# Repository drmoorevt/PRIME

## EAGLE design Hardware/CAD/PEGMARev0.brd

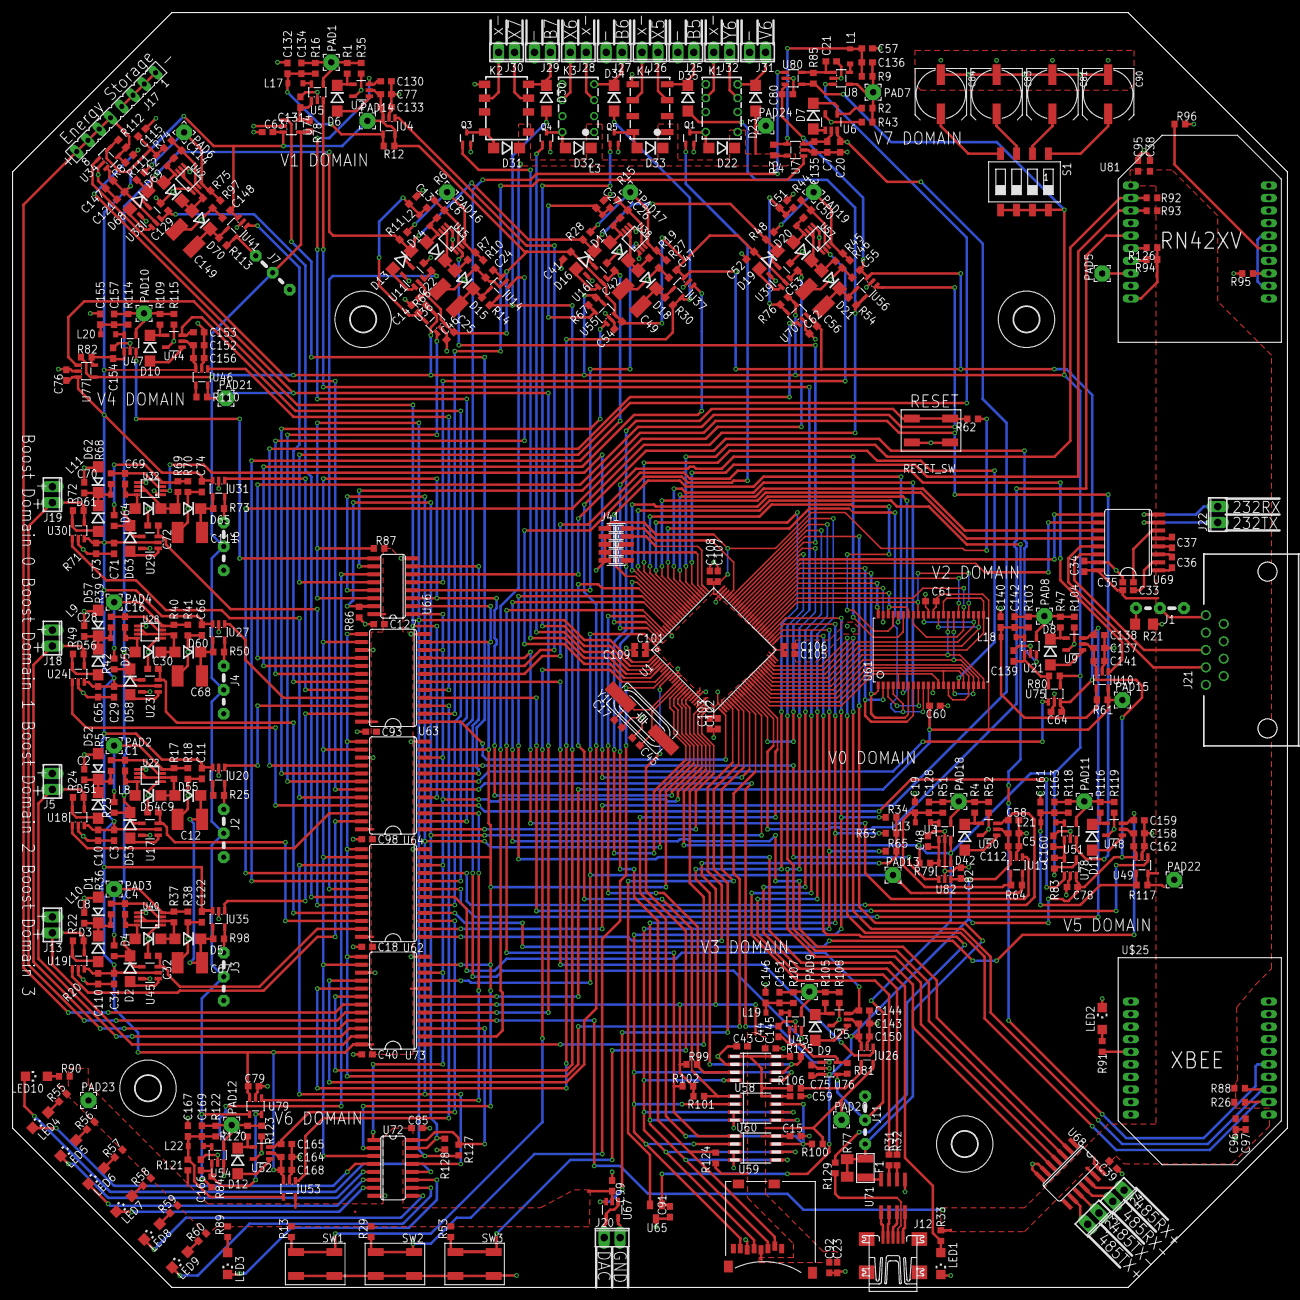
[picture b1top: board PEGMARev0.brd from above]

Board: 2 copper layers, 203.2 x 203.2 mm, 508 parts (0 on the bottom side), 341 nets.

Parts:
C1, C4, C6, C16, C26, C50, C69, C114: 4.7pF; C0603
C2, C8, C13, C27, C28, C51, C70, C115: 22uF; C0603
C3, C5, C7, C10, C11, C14, C15, C18, C24, C29, C31, C33, C34, C35, C36, C37, C38, C39, C40, C41, C44, C46, C47, C52, C54, C55, C59, C60, C61, C62, C63, C64, C65, C66, C71, C73, C74, C75, C76, C77, C78, C79, C80, C82, C85, C91, C92, C93, C96, C98, C99, C101, C102, C103, C105, C106, C107, C108, C109, C110, C112, C121, C122, C127, C133, C135, C137, C141, C143, C147, C148, C150, C152, C156, C158, C162, C164, C168: .1uF; C0603
C9, C19, C20, C22, C23, C30, C32, C42, C53, C57, C58, C72, C95, C97, C129, C130, C132, C138, C140, C144, C146, C153, C155, C159, C161, C165, C167: 10uF; C0603
C12, C25, C49, C56, C67, C68, C111, C149: 100uF Tantalum; C1812
C17, C45: 16pF; C0603
C21, C48, C131, C139, C145, C154, C160, C166: 4.7uF; C0603
C43: .22uF; C0603
C81, C83, C84, C90: 220uF; UD-8X10_NICHICON
C128, C134, C136, C142, C151, C157, C163, C169: 33pF; C0603
D1, D52, D57, D62: TPSMA11HE3; DO214AC
D2, D3, D4, D5, D6, D7, D8, D9, D10, D11, D12, D13, D14, D15, D16, D17, D18, D19, D20, D21, D22, D23, D30, D31, D32, D33, D34, D35, D42, D51, D53, D54, D55, D56, D58, D59, D60, D61, D63, D64, D65, D68, D69, D70: LSM115JE3; DO214BA
F1: MS-USMF010; FUSE(1210)
J1, J2, J3, J4, J6, J11: 04C
J5, J13, J18, J19, J20, J22, J23, J24, J25, J26, J27, J28, J29, J30, J31, J32: 2POL254
J7: Molex 22-28-4030; 04C
J12: MINI-USB-UX60A-MB-5ST; UX60A-MB-5ST
J17: FE08
J21: D-SUB9-H2M09RA; H2M09RA
J41: FTSH-105-02-F-D; 1296-10
K1: G6KU-2P-Y
K2: G6KU-2F-Y
K3: G6K-2P
K4: G6K-2G
L1, L2, L3, L4, L8, L9, L10, L11, L12, L13, L17, L18, L19, L20, L21, L22: 4.7uH; L1008/2520METRIC
LED1, LED2, LED3, LED4, LED5, LED6, LED7, LED8, LED9, LED10: CHIPLED_1206
PAD1, PAD2, PAD3, PAD4, PAD5, PAD6, PAD7, PAD8, PAD9, PAD10, PAD11, PAD12, PAD13, PAD14, PAD15, PAD16, PAD17, PAD18, PAD19, PAD20, PAD21, PAD22, PAD23, PAD24: 2,54/1,0
Q1, Q3, Q4, Q5: 2N2222; SOT323
R1, R2, R4, R47, R105, R109, R116, R120: 144k; R0603
R3, R82, R85, R110: .11; R0603
R5, R6, R15, R36, R39, R44, R68, R74: 150k; R0603
R7, R19, R45, R52: 180k; R0603
R8: 30; R0603
R9, R16, R51, R103, R107, R114, R118, R122: 360k; R0603
R10, R18, R27, R35, R38, R41, R43, R46, R70, R97, R104, R108, R115, R119, R123: 75k; R0603
R11, R28, R48: 22k; R0603
R12, R78: .263; R0603
R13, R29, R53, R55, R56, R57, R58, R59, R60, R89, R90: 1K; R0603
R14, R30, R54, R66, R67, R76: 0.10; R0603
R17, R37, R40, R69, R75: 125k; R0603
R20, R23, R42, R71, R111: 60k; R0603
R21: 120; R1206
R22, R98: .033; R0603
R24, R25: .044; R0603
R26, R88, R92, R93, R94, R95, R96, R126: 100k; R0603
R31, R32, R129: 22; R0603
R33, R91: 1k; R0603
R34, R62, R63, R65, R86, R87, R99, R100, R101, R102, R124, R125, R127, R128: 47k; R0603
R49, R50, R112, R113: .066; R0603
R61, R80: .22; R0603
R64, R79: .183; R0603
R72, R73: .132; R0603
R77: 120; M1206
R81, R106: .31; R0603
R83, R117: .174; R0603
R84, R121: .786; R0603
RESET_SW: B3SN-3012P; SWITCH(B3SN)
S1: CT2194MST; SMS-004
SW1, SW2, SW3: B3SN-3012P; SWITCH(B3SN)
U1: STM32F205VG; PZ100
U2, U6, U9, U11, U16, U17, U23, U25, U29, U33, U39, U44, U45, U48, U50, U52, U67: MCP601R; SOT23-5
U3, U5, U8, U21, U43, U47, U51, U54: TPS62240DDC; SOT23-5
U4, U7, U10, U13, U14, U18, U19, U20, U24, U26, U27, U30, U31, U34, U35, U36, U37, U41, U46, U49, U53, U55, U56, U70, U74, U75, U76, U77, U78, U79, U80, U82: MAX4376; SOT23-5
U12: Molex 500873-0816; MICROSD
U15, U22, U28, U32, U38, U40, U42, U57: LM2623; MSOP8
U58: HIH6130; SO-08M
U59, U60: 25AA512; SO-08M
U61: IS61WV51216-10ZSXI; TSOPII-Z44
U62, U63, U64, U73: 74HC4067; SO24W
U65: MAX6520; SOT23
U66, U72: 74HC259; SO16
U68: ADM3491ARZ; SO14
U69: MAX3232E; SO16L
U71: USB6B1; SO08
U81: RN42XV
U$1, U$2, U$3, U$4: 4,1
U$25: XBEE802.15.4; XBEE
Y1: HC49UP

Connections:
485_DE: U1.66, U68.4
!LED4: LED4.C, U72.4
!LED5: LED5.C, U72.5
!LED6: LED6.C, U72.6
!LED7: LED7.C, U72.7
!LED8: LED8.C, U72.9
!LED9: LED9.C, U72.10
!LED10: LED3.C, U72.11
!LED11: LED10.C, U72.12
!SW1: R13.1, SW1.3, SW1.4, U1.7
!SW2: R29.1, SW2.3, SW2.4, U1.8
!SW3: R53.1, SW3.3, SW3.4, U1.9
/RESET_MCU: J41.10, R62.2, RESET_SW.1, RESET_SW.2, U1.14
A16: U1.58, U61.43
A17: U1.59, U61.44
A18: U1.60, U61.28
ADC123_IN1: U1.24, U73.1
ADC123_IN2: U1.25, U64.1
ADC123_IN3: U1.26, U63.1
B0IN: D3.A, R22.2, U19.5
B0INRAW: J13.2, R22.1, U19.4, U73.23
B0LVEN: D2.C, D13.C, D16.C, D19.C, D53.C, D58.C, D63.C, D68.C, R11.1, R20.1, R23.1, R28.1, R42.1, R48.1, R71.1, R111.1, U11.4, U16.4, U17.4, U23.4, U29.4, U33.4, U39.4, U45.4
B0OUT: J3.1, R98.1, U35.5
B0OUTRAW: C12.1, C67.1, D5.C, D55.C, R98.2, U35.4
B1IN: D51.A, R24.2, U18.5
B1INRAW: J5.2, R24.1, U18.4, U73.22
B1OUT: J2.1, R25.1, U20.5
B1OUTRAW: R25.2, U20.4
B2IN: D56.A, R49.2, U24.5
B2INRAW: J18.2, R49.1, U24.4, U73.21
B2OUT: J4.1, R50.1, U27.5
B2OUTRAW: C68.1, D60.C, R50.2, U27.4
B3IN: D61.A, R72.2, U30.5
B3INRAW: J19.2, R72.1, U30.4, U73.20
B3OUT: J6.1, R73.1, U31.5
B3OUTRAW: C111.1, D65.C, R73.2, U31.4
B4IN: C115.2, L12.1, R74.2, R112.2, U34.5
B4INRAW: J17.5, J17.6, J17.7, J17.8, R8.2, R112.1, U34.4, U73.19
B4OUT: J7.1, R113.1, U41.5
B4OUTRAW: C149.1, D70.C, R113.2, U41.4
B5INRAW: C13.2, L2.1, R6.2, R66.1, U36.5
B5OUT: D30.A, R14.1, U14.5, U73.18
B5OUTRAW: C25.1, D15.C, R14.2, U14.4
B6INRAW: C27.2, L3.1, R15.2, R67.1, U55.5
B6OUT: D34.A, R30.1, U37.5, U73.17
B6OUTRAW: C49.1, D18.C, R30.2, U37.4
B7INRAW: C51.2, L4.1, R44.2, R76.1, U70.5
B7OUT: D35.A, R54.1, U56.5, U73.16
B7OUTRAW: C56.1, D21.C, R54.2, U56.4
BOOST4EN: U1.32, U32.2
BOOST5EN: U1.67, U15.2
BOOST6EN: U38.2, U66.4
BOOST7EN: U57.2, U66.5
BOOSTADJ0: C32.1, U45.3, U62.23
BOOSTADJ1: C9.1, U17.3, U62.22
BOOSTADJ2: C30.1, U23.3, U62.21
BOOSTADJ3: C72.1, U29.3, U62.20
BOOSTADJ4: C129.1, U33.3, U62.19
BOOSTADJ5: C22.1, U11.3, U62.18
BOOSTADJ6: C42.1, U16.3, U62.17
BOOSTADJ7: C53.1, U39.3, U62.16
BOOSTINCUR0: U19.1, U64.23
BOOSTINCUR1: U18.1, U64.22
BOOSTINCUR2: U24.1, U64.21
BOOSTINCUR3: U30.1, U64.20
BOOSTINCUR4: U34.1, U64.19
BOOSTINCUR5: U36.1, U64.18
BOOSTINCUR6: U55.1, U64.17
BOOSTINCUR7: U64.16, U70.1
BOOSTOUTCUR0: U35.1, U63.23
BOOSTOUTCUR1: U20.1, U63.22
BOOSTOUTCUR2: U27.1, U63.21
BOOSTOUTCUR3: U31.1, U63.20
BOOSTOUTCUR4: U41.1, U63.19
BOOSTOUTCUR5: U14.1, U63.18
BOOSTOUTCUR6: U37.1, U63.17
BOOSTOUTCUR7: U56.1, U63.16
BT_CTSRTS: U81.12, U81.16
BT_FRST: PAD5.1, U81.8
BT_RST: U1.36, U81.5
BUCKADJ0: C58.1, U50.3, U62.9
BUCKADJ1: C130.1, U2.3, U62.8
BUCKADJ2: C138.1, U9.3, U62.7
BUCKADJ3: C144.1, U25.3, U62.6
BUCKADJ4: C153.1, U44.3, U62.5
BUCKADJ5: C159.1, U48.3, U62.4
BUCKADJ6: C165.1, U52.3, U62.3
BUCKADJ7: C20.1, U6.3, U62.2
BUCKINCUR0: U64.9, U82.1
BUCKINCUR1: U64.8, U74.1
BUCKINCUR2: U64.7, U75.1
BUCKINCUR3: U64.6, U76.1
BUCKINCUR4: U64.5, U77.1
BUCKINCUR5: U64.4, U78.1
BUCKINCUR6: U64.3, U79.1
BUCKINCUR7: U64.2, U80.1
BUCKOUTCUR0: U13.1, U63.9
BUCKOUTCUR1: U4.1, U63.8
BUCKOUTCUR2: U10.1, U63.7
BUCKOUTCUR3: U26.1, U63.6
BUCKOUTCUR4: U46.1, U63.5
BUCKOUTCUR5: U49.1, U63.4
BUCKOUTCUR6: U53.1, U63.3
BUCKOUTCUR7: U7.1, U63.2
BUSVOUT: J2.2, J3.2, J4.2, J6.2, J7.2, J11.2, R66.2, R67.2, R76.2, R78.2, R79.2, R80.2, R81.2, R82.2, R83.2, R84.2, R85.2, S1.5, S1.6, S1.7, S1.8, U1.23, U3.3, U36.4, U55.4, U70.4, U74.4, U75.4, U76.4, U77.4, U78.4, U79.4, U80.4, U82.4
D0: U1.61, U61.1, U61.7
D1: U1.62, U61.2, U61.8
D2: U1.81, U61.3, U61.9
D3: U1.82, U61.4, U61.10
D4: U1.38, U61.5, U61.13
D5: U1.39, U61.14, U61.18
D6: U1.40, U61.15, U61.19
D7: U1.41, U61.16, U61.20
D8: U1.42, U61.21, U61.29
D9: U1.43, U61.22, U61.30
D10: U1.44, U61.23, U61.31
D11: U1.45, U61.24, U61.32
D12: U1.46, U61.25, U61.35
D13: U1.55, U61.26, U61.36
D14: U1.56, U61.27, U61.37
D15: U1.57, U61.38, U61.42
DACOUT1: U1.29, U62.1
DACOUT2: U1.30, U67.3
DOMEN: U1.15, U62.15, U66.13, U72.13
DOMLEN: R87.1, R127.1, U1.1, U66.14, U72.14
DOMRST: R86.1, R128.2, U1.34, U66.15, U72.15
DOMSEL0: U1.18, U62.10, U63.10, U64.10, U66.1, U72.1, U73.10
DOMSEL1: U1.16, U62.11, U63.11, U64.11, U66.2, U72.2, U73.11
DOMSEL2: U1.17, U62.14, U63.14, U64.14, U66.3, U72.3, U73.14
DOMSEL3: U1.33, U62.13, U63.13, U64.13, U73.13
EE0CS: R101.2, U1.91, U60.1
EE1CS: R102.2, U1.95, U59.1
EEHLD: R100.2, U1.37, U59.7, U60.7
EXTVREF: U1.31, U65.2
FSMC_BLN0: U1.97, U61.40
FSMC_BLN1: U1.98, U61.39
FSMC_NE1: U1.88, U61.6
FSMC_NOE: U1.85, U61.41
FSMC_NWE: U1.86, U61.17
HIHALM: R125.2, U1.84, U58.6
HIHCS: R99.2, U1.96, U58.3
JTCK: J41.4, U1.76
JTDI: J41.8, U1.77
JTDO: J41.6, U1.89
JTMS: J41.2, U1.72
K1EN: Q1.2, U1.5
K2EN: Q3.2, U1.4
K3EN: Q4.2, U1.3
K4EN: Q5.2, U1.2
MCUSCK: R65.1, U1.52, U12.5, U58.4, U59.6, U60.6
MCUSDI: R34.1, U1.54, U12.7, U58.5, U59.2, U60.2
MCUSDO: R63.1, U1.53, U12.3, U59.5, U60.5
MCUUSBD+: R32.1, U1.71
MCUUSBD-: R31.1, U1.70
unnamed: C131.1, R78.1, U5.1, U74.5
unnamed: C8.2, D1.C, D3.C, L10.1, R36.2
unnamed: J22.1, U69.7
unnamed: PAD3.1, R20.2, R37.1, R38.2, U40.4
unnamed: C4.1, R36.1, U40.3
unnamed: C2.2, D51.C, D52.C, L8.1, R5.2
unnamed: J22.2, U69.8
unnamed: C4.2, D4.A, L10.2, U40.8
unnamed: D42.C, R4.1, U50.4
unnamed: PAD16.1, R7.1, R10.2, R11.2, U15.4
unnamed: PAD2.1, R17.1, R18.2, R23.2, U22.4
unnamed: C1.1, R5.1, U22.3
unnamed: R126.2, U81.6
unnamed: C1.2, D54.A, L8.2, U22.8
unnamed: C6.1, R6.1, U15.3
unnamed: C6.2, D14.A, L2.2, U15.8
unnamed: L13.1, U3.5
unnamed: D7.C, R2.1, U6.4
unnamed: D4.C, D5.A, R37.2, U40.2, U40.6, U40.7
unnamed: D14.C, D15.A, R7.2, U15.6, U15.7
unnamed: D13.A, U11.1
unnamed: R94.2, U81.7
unnamed: R95.1, U81.13
unnamed: PAD17.1, R19.1, R27.2, R28.2, U38.4
unnamed: J1.2, J21.5
unnamed: C48.1, R79.1, U3.1, U82.5
unnamed: D54.C, D55.A, R17.2, U22.2, U22.6, U22.7
unnamed: D53.A, U17.1
unnamed: C33.1, U69.2
unnamed: C17.2, U1.12, Y1.2
unnamed: C45.1, U1.13, Y1.1
unnamed: D2.A, U45.1
unnamed: C136.2, PAD7.1, R2.2, R9.1, R43.2, U8.4
unnamed: L1.1, U8.5
unnamed: D31.A, K2.8, Q3.1
unnamed: C139.1, R80.1, U21.1, U75.5
unnamed: C26.1, R15.1, U38.3
unnamed: C26.2, D17.A, L3.2, U38.8
unnamed: D6.C, R1.1, U2.4
unnamed: D17.C, D18.A, R19.2, U38.6, U38.7
unnamed: D16.A, U16.1
unnamed: D7.A, U6.1
unnamed: C28.2, D56.C, D57.C, L9.1, R39.2
unnamed: PAD19.1, R45.1, R46.2, R48.2, U57.4
unnamed: C50.1, R44.1, U57.3
unnamed: PAD4.1, R40.1, R41.2, R42.2, U28.4
unnamed: C35.1, U69.6
unnamed: C36.1, U69.1
unnamed: C36.2, U69.3
unnamed: C37.1, U69.4
unnamed: C16.1, R39.1, U28.3
unnamed: C16.2, D59.A, L9.2, U28.8
unnamed: C37.2, U69.5
unnamed: J21.3, U69.14
unnamed: J21.2, U69.13
unnamed: D59.C, D60.A, R40.2, U28.2, U28.6, U28.7
unnamed: J1.3, R21.2
unnamed: D22.A, K1.8, Q1.1
unnamed: C134.2, PAD1.1, R1.2, R16.1, R35.2, U5.4
unnamed: C50.2, D20.A, L4.2, U57.8
unnamed: D20.C, D21.A, R45.2, U57.6, U57.7
unnamed: D19.A, U39.1
unnamed: LED3.A, R89.1
unnamed: C145.1, R81.1, U43.1, U76.5
unnamed: D58.A, U23.1
unnamed: C154.1, R82.1, U47.1, U77.5
unnamed: C160.1, R83.1, U51.1, U78.5
unnamed: C128.2, PAD18.1, R4.2, R51.1, R52.2, U3.4
unnamed: C166.1, R84.1, U54.1, U79.5
unnamed: C21.1, R85.1, U8.1, U80.5
unnamed: C83.+, S1.3
unnamed: C90.+, S1.1
unnamed: C81.+, S1.2
unnamed: LED4.A, R55.1
unnamed: LED5.A, R56.1
unnamed: LED6.A, R57.1
unnamed: LED10.A, R90.1
unnamed: C84.+, S1.4
unnamed: J12.4, R129.2
unnamed: C70.2, D61.C, D62.C, L11.1, R68.2
unnamed: LED7.A, R58.1
unnamed: LED8.A, R59.1
unnamed: LED9.A, R60.1
unnamed: R69.1, R70.2, R71.2, U32.4
unnamed: C69.1, R68.1, U32.3
unnamed: C69.2, D64.A, L11.2, U32.8
unnamed: D64.C, D65.A, R69.2, U32.6, U32.7
unnamed: D63.A, U29.1
unnamed: L17.1, U5.5
unnamed: D6.A, U2.1
unnamed: PAD6.1, R75.1, R97.2, R111.2, U42.4
unnamed: J20.1, U67.1, U67.4
unnamed: C114.1, R74.1, U42.3
unnamed: C114.2, D69.A, L12.2, U42.8
unnamed: D69.C, D70.A, R75.2, U42.2, U42.6, U42.7
unnamed: J32.1, K1.3
unnamed: D68.A, U33.1
unnamed: J32.2, K1.6
unnamed: D32.A, K3.8, Q4.1
unnamed: J28.1, K3.3
unnamed: D23.C, J31.1, K1.4
unnamed: J28.2, K3.6
unnamed: D33.A, K4.8, Q5.1
unnamed: J30.1, K2.3
unnamed: D30.C, J29.1, K2.4
unnamed: J30.2, K2.6
unnamed: R91.1, U$25.15
unnamed: LED2.A, R91.2
unnamed: D34.C, J27.1, K3.4
unnamed: R96.1, U81.15
unnamed: D35.C, J25.1, K4.4
unnamed: J26.1, K4.3
unnamed: J26.2, K4.6
unnamed: D8.C, R47.1, U9.4
unnamed: J24.1, U68.12
unnamed: J24.2, U68.11
unnamed: J23.1, U68.10
unnamed: J23.2, U68.9
unnamed: J12.1, U71.1
unnamed: J12.2, U71.2
unnamed: J12.3, U71.3
unnamed: J12.5, U71.4
unnamed: C142.2, PAD8.1, R47.2, R103.1, R104.2, U21.4
unnamed: L18.1, U21.5
unnamed: D8.A, U9.1
unnamed: D42.A, U50.1
unnamed: D9.C, R105.1, U25.4
unnamed: C151.2, PAD9.1, R105.2, R107.1, R108.2, U43.4
unnamed: L19.1, U43.5
unnamed: D9.A, U25.1
unnamed: D10.C, R109.1, U44.4
unnamed: C157.2, PAD10.1, R109.2, R114.1, R115.2, U47.4
unnamed: L20.1, U47.5
unnamed: D10.A, U44.1
unnamed: D11.C, R116.1, U48.4
unnamed: C163.2, PAD11.1, R116.2, R118.1, R119.2, U51.4
unnamed: L21.1, U51.5
unnamed: D11.A, U48.1
unnamed: D12.C, R120.1, U52.4
unnamed: C169.2, PAD12.1, R120.2, R122.1, R123.2, U54.4
unnamed: L22.1, U54.5
unnamed: D12.A, U52.1
PE: C2.1, C3.1, C5.1, C7.1, C8.1, C9.2, C10.1, C11.1, C12.2, C13.1, C14.1, C15.1, C17.1, C18.1, C19.2, C20.2, C21.2, C22.2, C23.1, C24.1, C25.2, C27.1, C28.1, C29.1, C30.2, C31.1, C32.2, C34.2, C35.2, C38.1, C39.2, C40.1, C41.1, C42.2, C43.1, C44.1, C45.2, C46.1, C47.1, C48.2, C49.2, C51.1, C52.1, C53.2, C54.1, C55.1, C56.2, C57.2, C58.2, C59.1, C60.1, C61.1, C62.1, C63.1, C64.1, C65.1, C66.1, C67.2, C68.2, C70.1, C71.1, C72.2, C73.1, C74.1, C75.1, C76.1, C77.1, C78.1, C79.1, C80.1, C81.-, C82.1, C83.-, C84.-, C85.1, C90.-, C91.1, C92.2, C93.1, C95.1, C96.1, C97.1, C98.1, C99.1, C101.1, C102.1, C103.1, C105.1, C106.1, C107.1, C108.1, C109.1, C110.1, C111.2, C112.1, C115.1, C121.1, C122.1, C127.1, C129.2, C130.2, C131.2, C132.2, C133.1, C135.1, C137.1, C138.2, C139.2, C140.2, C141.1, C143.1, C144.2, C145.2, C146.2, C147.1, C148.1, C149.2, C150.1, C152.1, C153.2, C154.2, C155.2, C156.1, C158.1, C159.2, C160.2, C161.2, C162.1, C164.1, C165.2, C166.2, C167.2, C168.1, D1.A, D52.A, D57.A, D62.A, J5.1, J13.1, J17.1, J17.2, J17.3, J17.4, J18.1, J19.1, J20.2, J25.2, J27.2, J29.2, J31.2, J41.3, J41.5, J41.7, J41.9, K1.5, K2.5, K3.5, K4.5, LED1.C, LED2.C, Q1.3, Q3.3, Q4.3, Q5.3, R10.1, R18.1, R21.1, R27.1, R35.1, R38.1, R41.1, R43.1, R46.1, R52.1, R70.1, R86.2, R94.1, R95.2, R96.2, R97.1, R104.1, R108.1, R115.1, R119.1, R123.1, R126.1, R128.1, RESET_SW.3, RESET_SW.4, SW1.1, SW1.2, SW2.1, SW2.2, SW3.1, SW3.2, U1.10, U1.20, U1.27, U1.74, U1.94, U2.5, U3.2, U4.2, U5.2, U6.5, U7.2, U8.2, U9.5, U10.2, U11.5, U12.6, U13.2, U14.2, U15.1, U15.5, U16.5, U17.5, U18.2, U19.2, U20.2, U21.2, U22.1, U22.5, U23.5, U24.2, U25.5, U26.2, U27.2, U28.1, U28.5, U29.5, U30.2, U31.2, U32.1, U32.5, U33.5, U34.2, U35.2, U36.2, U37.2, U38.1, U38.5, U39.5, U40.1, U40.5, U41.2, U42.1, U42.5, U43.2, U44.5, U45.5, U46.2, U47.2, U48.5, U49.2, U50.5, U51.2, U52.5, U53.2, U54.2, U55.2, U56.2, U57.1, U57.5, U58.2, U59.3, U59.4, U60.3, U60.4, U61.12, U61.34, U62.12, U63.12, U63.15, U64.12, U64.15, U65.3, U66.8, U67.5, U68.6, U68.7, U69.15, U70.2, U71.5, U72.8, U73.12, U73.15, U74.2, U75.2, U76.2, U77.2, U78.2, U79.2, U80.2, U81.10, U82.2, U$25.10
RAWV0: C19.1, C128.1, L13.2, R51.2, R64.2, U13.4
RAWV1: C132.1, C134.1, L17.2, R12.2, R16.2, U4.4
RAWV2: C140.1, C142.1, L18.2, R61.2, R103.2, U10.4
RAWV3: R106.2, U26.4
RAWV4: R110.2, U46.4
RAWV5: C161.1, C163.1, L21.2, R117.2, R118.2, U49.4
RAWV6: C167.1, C169.1, L22.2, R121.2, R122.2, U53.4
RAWV7: C57.1, C136.1, L1.2, R3.2, R9.2, U7.4
SDCS: R124.2, U1.90, U12.2
UART1RX: U1.93, U68.2
UART1TX: U1.92, U68.5
UART3RX: R26.1, U1.48, U$25.2
UART3TX: R88.1, U1.47, U$25.3
UART4RX: R92.1, U1.79, U81.2
UART4TX: R93.1, U1.78, U81.3
UART5RX: U1.83, U69.12
UART5TX: U1.80, U69.11
UART6RX: U1.64, U69.9
UART6TX: U1.63, U69.10
USB5V_F: F1.P$1, J11.3, R77.1, R77.2, U1.68
USBD+: R32.2, U71.6
USBD-: R31.2, U71.7
USBLED: LED1.A, R33.2, U1.69
USB_ID: R129.1, U1.51
V0: C101.2, C102.2, C103.2, C105.2, C106.2, C107.2, C108.2, C109.2, J41.1, PAD13.1, R62.1, R64.1, U1.6, U1.11, U1.19, U1.22, U1.28, U1.49, U1.50, U1.73, U1.75, U1.100, U13.5, U73.9
V1: C3.2, C5.2, C7.2, C10.2, C11.2, C14.2, C18.2, C24.2, C29.2, C31.2, C40.2, C41.2, C46.2, C47.2, C52.2, C54.2, C55.2, C62.2, C63.2, C64.2, C65.2, C66.2, C71.2, C73.2, C74.2, C75.2, C76.2, C77.2, C78.2, C79.2, C80.2, C82.2, C91.2, C93.2, C98.2, C110.2, C112.2, C121.2, C122.2, C127.2, C133.2, C135.2, C137.2, C141.2, C143.2, C147.2, C148.2, C150.2, C152.2, C156.2, C158.2, C162.2, C164.2, C168.2, PAD14.1, R12.1, R87.2, U2.2, U4.3, U4.5, U6.2, U7.3, U9.2, U10.3, U11.2, U13.3, U14.3, U16.2, U17.2, U18.3, U19.3, U20.3, U23.2, U24.3, U25.2, U26.3, U27.3, U29.2, U30.3, U31.3, U33.2, U34.3, U35.3, U36.3, U37.3, U39.2, U41.3, U44.2, U45.2, U46.3, U48.2, U49.3, U50.2, U52.2, U53.3, U55.3, U56.3, U62.24, U63.24, U64.24, U65.1, U66.16, U70.3, U73.8, U73.24, U74.3, U75.3, U76.3, U77.3, U78.3, U79.3, U80.3, U82.3
V1EN: U1.35, U5.3
V2: C60.2, C61.2, PAD15.1, R61.1, U10.5, U61.11, U61.33, U73.7
V2EN: U21.3, U66.6
V3: C15.2, C23.2, C43.2, C44.2, C59.2, C92.1, PAD20.1, R34.2, R63.2, R65.2, R99.1, R100.1, R101.1, R102.1, R106.1, R124.1, R125.1, U12.4, U26.5, U58.1, U58.8, U59.8, U60.8, U73.6
V3EN: U43.3, U66.7
V3RAW: C146.1, C151.1, L19.2, R107.2
V4: PAD21.1, R8.1, R110.1, U46.5, U73.5
V4EN: U47.3, U66.9
V4RAW: C155.1, C157.1, L20.2, R114.2
V5: C33.2, C34.1, C38.2, C39.1, C95.2, C96.2, C97.2, PAD22.1, R26.2, R33.1, R88.2, R92.2, R93.2, R117.1, U49.5, U68.13, U68.14, U69.16, U73.4, U81.1, U$25.1
V5EN: U51.3, U66.10
V6: C85.2, C99.2, PAD23.1, R13.2, R29.2, R53.2, R55.2, R56.2, R57.2, R58.2, R59.2, R60.2, R89.2, R90.2, R121.1, R127.2, U53.5, U67.2, U72.16, U73.3
V6EN: U54.3, U66.11
V7: D22.C, D23.A, D31.C, D32.C, D33.C, K1.1, K2.1, K3.1, K4.1, PAD24.1, R3.1, U7.5, U73.2
V7EN: U8.3, U66.12
VUSB: F1.P$2, U71.8
XBE_RST: U1.87, U$25.5
~485_RE: U1.65, U68.3

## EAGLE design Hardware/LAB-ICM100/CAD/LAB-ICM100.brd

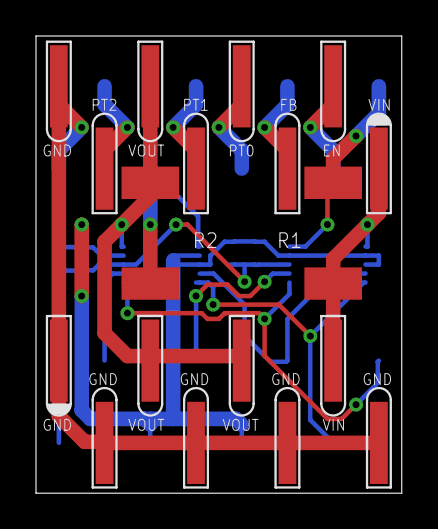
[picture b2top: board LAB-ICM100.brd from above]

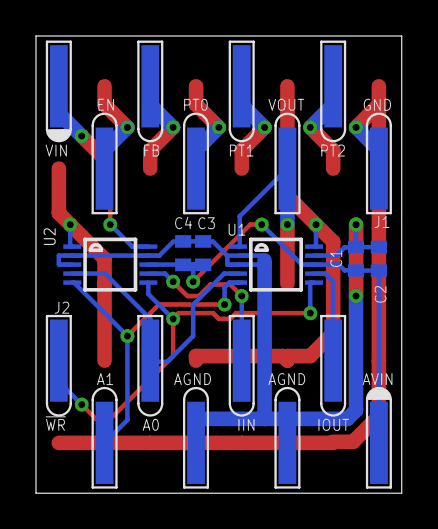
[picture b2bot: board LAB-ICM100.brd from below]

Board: 2 copper layers, 20.3 x 25.4 mm, 12 parts (8 on the bottom side), 17 nets.

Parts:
C1, C3: .1uF; C0402
C2, C4: 10uF; C0402
J1, J2: SULLINSSMTPINHEADER-8; SMTHEADER-8
J3, J4: SMTHEADER-8
R1, R2: 1; R2512
U1, U2: AD8253; MSOP10

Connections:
!AN_WR: J2.P$8, U1.6, U2.6
AN_A0: J2.P$6, U1.4, U2.4
AN_A1: J2.P$7, U1.5, U2.5
AN_GND: C1.2, C2.2, C3.2, C4.2, J2.P$3, J2.P$5, U1.2, U1.3, U1.9, U2.2, U2.3, U2.9
AN_IIN: J2.P$4, U2.7
AN_IOUT: J2.P$2, U1.7
AN_VIN: C1.1, C2.1, C3.1, C4.1, J2.P$1, U1.8, U2.8
BRD_VIN: J1.P$1, R1.1, U2.10
BRD_VOUT: J1.P$6, R2.1, U1.1
PSU_EN: J1.P$2, J3.P$2
PSU_FB: J1.P$3, J3.P$3
PSU_GND: J1.P$8, J3.P$8, J4.P$1, J4.P$2, J4.P$4, J4.P$6, J4.P$8
PSU_PT0: J1.P$4, J3.P$4
PSU_PT1: J1.P$5, J3.P$5
PSU_PT2: J1.P$7, J3.P$7
PSU_VIN: J3.P$1, J4.P$7, R1.2, U2.1
PSU_VOUT: J3.P$6, J4.P$3, J4.P$5, R2.2, U1.10
